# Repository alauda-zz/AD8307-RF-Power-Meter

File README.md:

# AD8307-RF-Power-Meter
AD8307 RF Power Meter
Release version Rev1.0

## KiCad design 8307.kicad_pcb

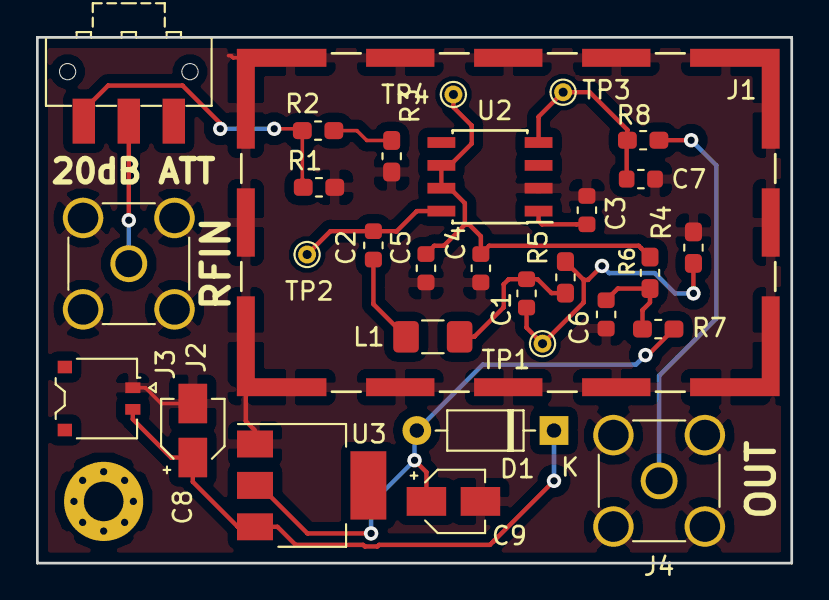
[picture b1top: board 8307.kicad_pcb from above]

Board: 2 copper layers, 41.9 x 29.2 mm, 30 parts (0 on the bottom side), 15 nets.

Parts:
C1: 15p; C_0603_1608Metric
C2, C5: 10n; C_0603_1608Metric
C3, C4, C6: 100n; C_0603_1608Metric
C7: 1n; C_0603_1608Metric
C8: 10u; CP_Elec_3x5.3
C9: 22u; CP_Elec_3x5.3
D1: 1N4148; D_DO-35_SOD27_P7.62mm_Horizontal
J1: RF_Shield_One_Piece; Laird_Technologies_BMI-S-209-F_29.36x18.50mm
J2, J4: Conn_Coaxial; SMA_Amphenol_901-144_Vertical
J3: Conn_01x02_Female; JST_ACH_BBM02B-ACHSS-GAN-ETF_1x02-1MP_P1.20mm_Vertical
L1: 7nH; L_1206_3216Metric_Pad1.42x1.75mm_HandSolder
R1, R3: 61; R_0603_1608Metric_Pad1.05x0.95mm_HandSolder
R2: 248; R_0603_1608Metric_Pad1.05x0.95mm_HandSolder
R4: 53; R_0603_1608Metric_Pad1.05x0.95mm_HandSolder
R5: 470; R_0603_1608Metric_Pad1.05x0.95mm_HandSolder
R6: 22; R_0603_1608Metric_Pad1.05x0.95mm_HandSolder
R7: 110; R_0603_1608Metric_Pad1.05x0.95mm_HandSolder
R8: 220; R_0603_1608Metric_Pad1.05x0.95mm_HandSolder
SW1: SW_DPDT_x2; SW_SPDT_CK-JS102011SAQN
TP1, TP2, TP3, TP4: TestPoint; TestPoint_THTPad_D1.0mm_Drill0.5mm
U2: AD8307; SOIC-8_3.9x4.9mm_P1.27mm
U3: LT1117-5.0; SOT-223

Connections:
/+5_VCC: C6.1, R6.1, R7.1
GND: C3.2, C4.2, C5.2, C6.2, C7.2, C8.2, C9.2, J1.1, J2.2, J3.1, J4.2, R1.2, R3.2, R4.2, U2.2, U3.1
unnamed: C1.1, L1.1, R5.1
unnamed: C1.2, R4.1, R5.2, TP1.1
unnamed: C2.1, TP2.1, U2.8
unnamed: C2.2, L1.2
unnamed: C3.1, U2.1
unnamed: C4.1, C5.1, R6.2, TP4.1, U2.6, U2.7
unnamed: C7.1, R8.2, TP3.1, U2.4
unnamed: C8.1, D1.1, J3.2, U3.3
unnamed: C9.1, D1.2, R7.2, U3.2
unnamed: J2.1, SW1.2
unnamed: J4.1, R8.1
unnamed: R1.1, R2.2, SW1.3
unnamed: R2.1, R3.1

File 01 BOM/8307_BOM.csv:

"Id";"Designator";"Package";"Quantity";"Designation";"Supplier and ref";
1;"C1";"C_0603_1608Metric";1;"15p";;;
2;"C5,C2";"C_0603_1608Metric";2;"10n";;;
3;"C7";"C_0603_1608Metric";1;"1n";;;
4;"TP4,TP3,TP2,TP1";"TestPoint_THTPad_D1.0mm_Drill0.5mm";4;"TestPoint";;;
5;"R8";"R_0603_1608Metric_Pad1.05x0.95mm_HandSolder";1;"220";;;
6;"R7";"R_0603_1608Metric_Pad1.05x0.95mm_HandSolder";1;"110";;;
7;"R6";"R_0603_1608Metric_Pad1.05x0.95mm_HandSolder";1;"22";;;
8;"R5";"R_0603_1608Metric_Pad1.05x0.95mm_HandSolder";1;"470";;;
9;"R4";"R_0603_1608Metric_Pad1.05x0.95mm_HandSolder";1;"53";;;
10;"R3,R1";"R_0603_1608Metric_Pad1.05x0.95mm_HandSolder";2;"61";;;
11;"R2";"R_0603_1608Metric_Pad1.05x0.95mm_HandSolder";1;"248";;;
12;"C6,C4,C3";"C_0603_1608Metric";3;"100n";;;
13;"J3";"JST_ACH_BBM02B-ACHSS-GAN-ETF_1x02-1MP_P1.20mm_Vertical";1;"Conn_01x02_Female";;;
14;"J1";"Laird_Technologies_BMI-S-209-F_29.36x18.50mm";1;"RF_Shield_One_Piece";;;
15;"J4,J2";"SMA_Amphenol_901-144_Vertical";2;"Conn_Coaxial";;;
16;"C9";"CP_Elec_3x5.3";1;"22u";;;
17;"C8";"CP_Elec_3x5.3";1;"10u";;;
18;"D1";"D_DO-35_SOD27_P7.62mm_Horizontal";1;"1N4148";;;
19;"SW1";"SW_SPDT_CK-JS102011SAQN";1;"SW_DPDT_x2";;;
20;"L1";"L_1206_3216Metric_Pad1.42x1.75mm_HandSolder";1;"7nH";;;
21;"U3";"SOT-223";1;"LT1117-5.0";;;
22;"U2";"SOIC-8_3.9x4.9mm_P1.27mm";1;"AD8307";;;
23;"REF**";"MountingHole_2.2mm_M2_Pad_Via";1;"MountingHole_2.2mm_M2_Pad_Via";;;

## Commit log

2019-02-16 Initial
2019-02-16 Release Revision 1-0 of project 8307 RF Power Sensor
2019-02-16 Added Readme
2019-02-16 Adăugat printout-uri (pdf) - schemă, layere etc
2019-02-20 Am modificat plot-urile de Fabrication și am actualizat Excel-ul cu BOM-ul - verificat dacă am primit componentele corecte. Am descoperit mai multe probleme pe placă. Probabil o să trebuiască să cree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
2019-02-20 Am făcut sursa de documente publică (GitHub) și am modificat ceva documente; atenție, versiunea 1 are o eroare.
2019-02-20 Cleanup
